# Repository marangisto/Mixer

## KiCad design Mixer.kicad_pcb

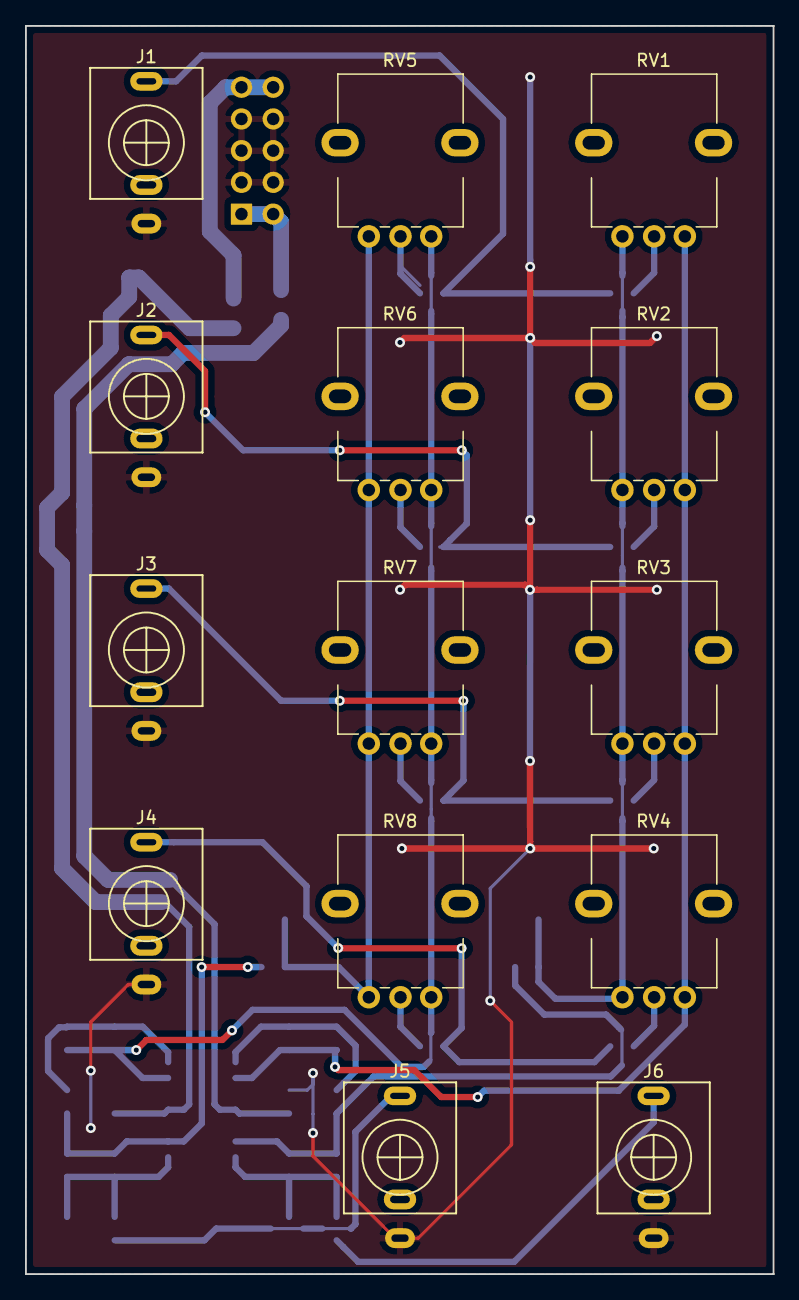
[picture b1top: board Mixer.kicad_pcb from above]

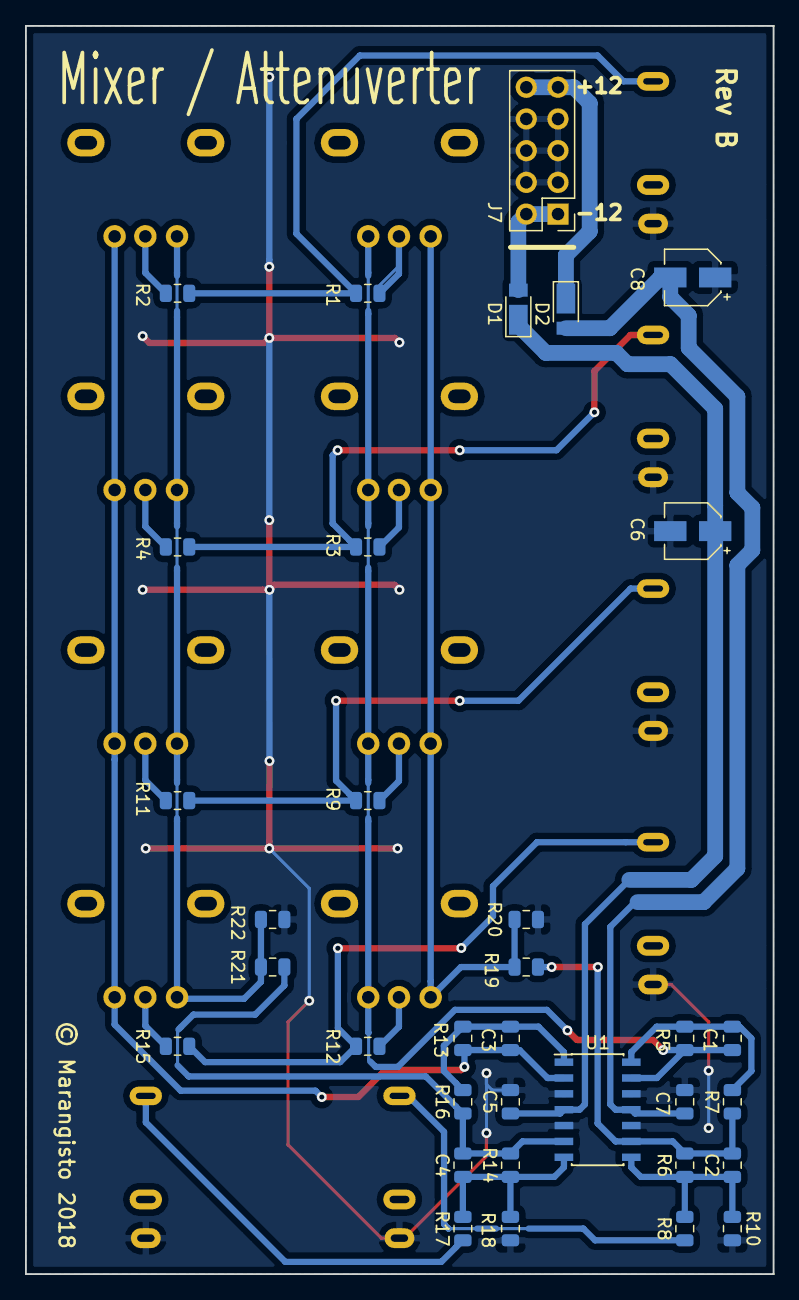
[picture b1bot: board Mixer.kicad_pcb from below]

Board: 2 copper layers, 59.9 x 100.0 mm, 48 parts (34 on the bottom side), 29 nets.

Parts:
C1, C2, C3, C4: 47p; C_0805_2012Metric
C5, C7: 100n; C_0805_2012Metric
C6, C8: 10u; CP_Elec_4x5.8
D1, D2: DFLR1400-7; D_PowerDI-123
J1, J2, J3, J4, J5, J6: AudioJack2_Ground_Switch; PJ398SM
J7: Conn_02x05_Odd_Even; PinHeader_2x05_P2.54mm_Vertical
R1, R2, R3, R4, R5, R6, R7, R9, R10, R11, R12, R13, R14, R15, R16, R18: 100k; R_0805_2012Metric
R8, R17: 1k; R_0805_2012Metric
R19, R21: 0; R_0805_2012Metric
R20, R22: 1G; R_0805_2012Metric
RV1, RV2, RV3, RV4, RV5, RV6, RV7, RV8: 50k; AlpsRK09K
U1: TL074; SOIC-14_3.9x8.7mm_P1.27mm

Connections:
+12VA: C5.1, C6.1, D1.1, U1.4
-12VA: C7.2, C8.2, D2.2, U1.11
GND: C5.2, C6.2, C7.1, C8.1, J1.S, J2.S, J3.S, J4.S, J5.S, J6.S, J7.3, J7.4, J7.5, J7.6, J7.7, J7.8, R10.2, R18.2, R20.2, R22.2, U1.3, U1.5, U1.10, U1.12
unnamed: C1.1, R5.1, R7.2, U1.14
unnamed: C1.2, R5.2, RV5.1, RV6.1, RV7.1, RV8.1, U1.13
unnamed: C2.1, R6.1, R8.2, R10.1, U1.8
unnamed: C2.2, R6.2, R7.1, R19.1, U1.9
unnamed: C3.1, R13.1, R16.2, U1.1
unnamed: C3.2, R13.2, RV1.1, RV2.1, RV3.1, RV4.1, U1.2
unnamed: C4.1, R14.1, R17.2, R18.1, U1.7
unnamed: C4.2, R14.2, R16.1, R21.1, U1.6
unnamed: D1.2, J7.1, J7.2
unnamed: D2.1, J7.9, J7.10
unnamed: J1.T, R1.2, R2.2
unnamed: J2.T, R3.2, R4.2
unnamed: J3.T, R9.2, R11.2
unnamed: J4.T, R12.2, R15.2
unnamed: J5.T, R8.1
unnamed: J6.T, R17.1
unnamed: R1.1, RV5.2
unnamed: R2.1, RV1.2
unnamed: R3.1, RV6.2
unnamed: R4.1, RV2.2
unnamed: R9.1, RV7.2
unnamed: R11.1, RV3.2
unnamed: R12.1, RV8.2
unnamed: R15.1, RV4.2
unnamed: R19.2, R20.1, RV5.3, RV6.3, RV7.3, RV8.3
unnamed: R21.2, R22.1, RV1.3, RV2.3, RV3.3, RV4.3

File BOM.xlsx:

/home/marten/Mixer/Mixer.sch
Mon Jul 23 20:08:47 2018
Eeschema 4.0.7-e2-6376~58~ubuntu16.04.1
Component Count:44
Ref | Qnty | Value | Part | Footprint | Description | Vendor | Price | Total
C1, C2, C3, C4 | 4 | 47p | device:C | Capacitors_SMD:C_0805 | Unpolarized capacitor |  | 0.03 | 0.12
C5, C7 | 2 | 100n | device:C | Capacitors_SMD:C_0805 | Unpolarized capacitor |  | 0.03 | 0.06
C6, C8 | 2 | 10u | device:CP | Capacitors_SMD:CP_Elec_4x5.8 | Polarised capacitor |  | 0.26 | 0.52
D1, D2 | 2 | DFLR1400-7 | device:D | Diodes_SMD:D_PowerDI-123 | Diode |  | 0.236 | 0.472
J1, J3, J4, J5, J6, J7 | 6 | Audio-Jack-2_Switch | conn:Audio-Jack-2_Switch | DTD:PJ398SM | 2-pin audio jack receptable (mono/TS connector) with switching contact |  |  | 0
J2 | 1 | Conn_02x05_Odd_Even | conn:Conn_02x05_Odd_Even | Pin_Headers:Pin_Header_Straight_2x05_Pitch2.54mm | Generic connector, double row, 02x05, odd/even pin numbering scheme (row 1 odd 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 |  |  | 0
R1, R2, R3, R4, R5, R6, R7, R9, R10, R11, R12, R13, R14, R15, R16, R18 | 16 | 100k | device:R | Resistors_SMD:R_0805 | Resistor |  | 0.009 | 0.144
R8, R17 | 2 | 1k | device:R | Resistors_SMD:R_0805 | Resistor |  | 0.005 | 0.01
RV1, RV2, RV3, RV4, RV5, RV6, RV7, RV8 | 8 | 47k | device:POT | Potentiometers:Potentiometer_Alps_RK09K_Horizontal | Potentiometer |  |  | 0
U1 | 1 | TL074 | linear:TL074 | Housings_SOIC:SOIC-14_3.9x8.7mm_Pitch1.27mm | Low-Power, Quad-Operational Amplifiers, DIP-14/SOIC-14/SSOP-14 |  | 0.694 | 0.694
 | 44 |  |  |  |  |  |  | 2.02

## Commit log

2018-07-23 Initial Mixer commit.
2018-07-23 Updated BOM.
2018-07-25 Fixed DRC violation.
2018-07-26 Added configuration resistors.
2018-07-26 Silkscreen, edge-cuts and branding.
2018-07-26 Added rendering.
2018-07-26 Posted gerbers.
2018-07-28 Corrected power pins for TL074, now Rev B.
2018-07-31 Spreadsheet BOM.
2018-08-04 Upgraded to KiCad 5.
2018-08-04 Updated footprints.
2018-08-15 Revert "Updated footprints."
    This reverts commit 2671d91becb9144079156a1e4aa2e05ff666f7ae.
2018-08-15 Revert "Upgraded to KiCad 5."
    This reverts commit 56dcfc32eec30f0ad305eafc7c7b25461d825fe0.
2018-08-15 This is revision B of the board.
2018-08-16 Updated silk-screen with voltages.

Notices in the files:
Mixer.kicad_pcb:
© Marangisto 2018
